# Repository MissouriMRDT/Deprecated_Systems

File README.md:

<<<<<<< HEAD
# Deprecated-Systems
 Deprecated sub-system repositories that have no present day equivalent

How to add repos to this: 

1) Make branch on here for the repo you're about to copy in
2) Clone this repo onto your pc
3) Make sure that you've merged all branches on the deprecated repo into master, this process only preserves its master
4) in gitshell inside of the Deprecated-Systems folder:

git checkout [name of branch you're going to copy the repo into]

git remote add x [url of deprecated repo]

git fetch x

git merge x/master --allow-unrelated-histories

git remote rm x

5) delete old branch

=======
Battery-Management-System
=========================

Battery Management System with integrated CC and CV charge control and passive cell balancing.
>>>>>>> x/master

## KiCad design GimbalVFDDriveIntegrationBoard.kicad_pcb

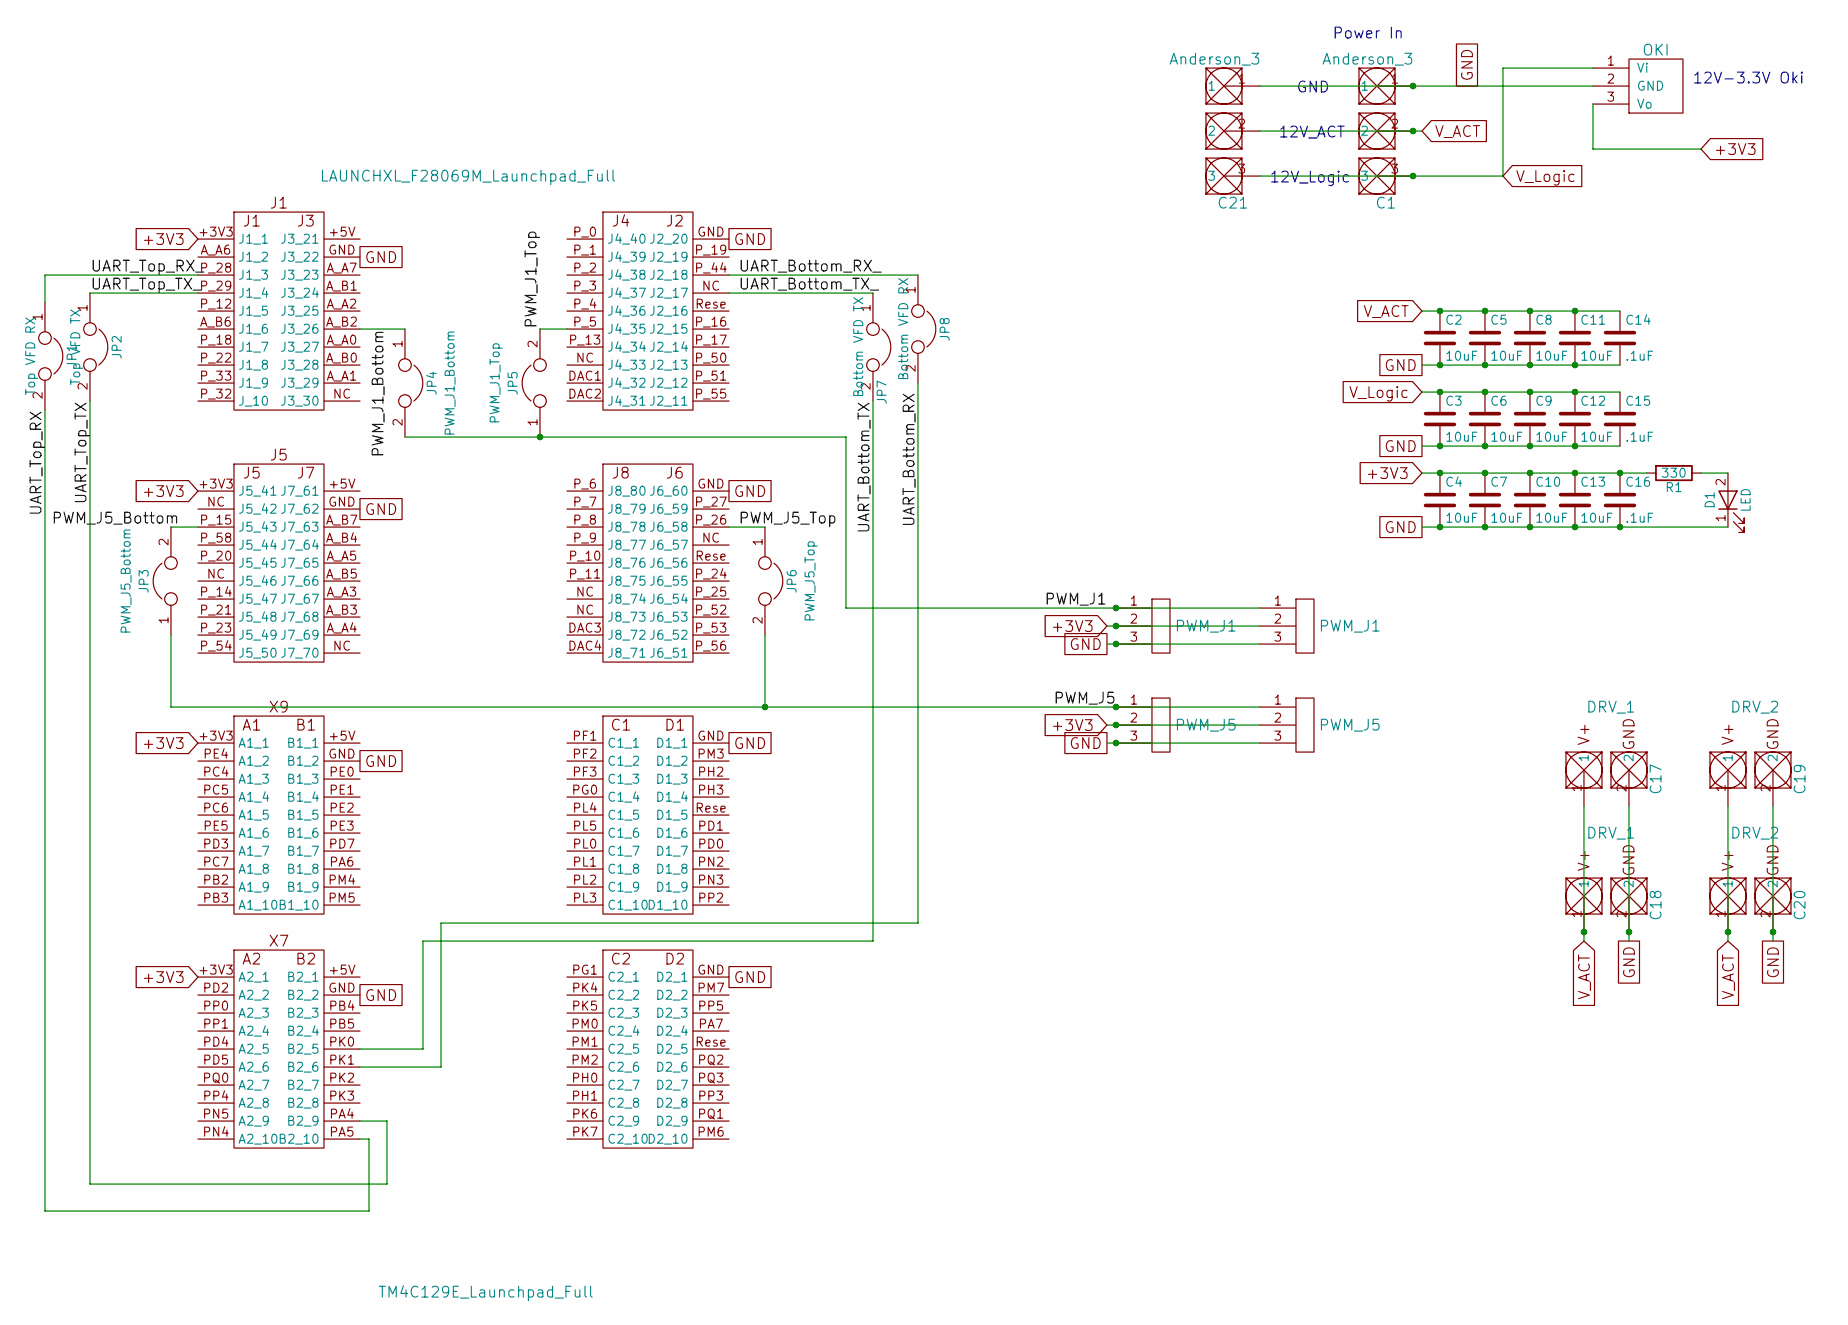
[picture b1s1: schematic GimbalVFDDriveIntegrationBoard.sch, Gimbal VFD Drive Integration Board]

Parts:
C1, C21: Anderson_3; Anderson_3_Horisontal_Side_by_Side
C2, C3, C4, C5, C6, C7, C8, C9, C10, C11, C12, C13: 10uF; C_0603_HandSoldering
C14, C15, C16: .1uF; C_0603_HandSoldering
C17, C18: DRV_1; Anderson_2_Horisontal_Side_by_Side
C19, C20: DRV_2; Anderson_2_Horisontal_Side_by_Side
D1: LED; LED_1206_HandSoldering
JP1: Top VFD RX; Pin_Header_Straight_1x02_Pitch1.27mm
JP2: Top VFD TX; Pin_Header_Straight_1x02_Pitch1.27mm
JP3: PWM_J5_Bottom; Pin_Header_Straight_1x02_Pitch1.27mm
JP4: PWM_J1_Bottom; Pin_Header_Straight_1x02_Pitch1.27mm
JP5: PWM_J1_Top; Pin_Header_Straight_1x02_Pitch1.27mm
JP6: PWM_J5_Top; Pin_Header_Straight_1x02_Pitch1.27mm
JP7: Bottom VFD TX; Pin_Header_Straight_1x02_Pitch1.27mm
JP8: Bottom VFD RX; Pin_Header_Straight_1x02_Pitch1.27mm
R1: 330; R_0603_HandSoldering
U1: LAUNCHXL_F28069M_Launchpad_Full; LAUNCHXL_F28069M_Launchpad_FULL_Booster_SMD
U2: TM4C129E_Launchpad_Full; TM4C129E_Launchpad_FULL_Booster_Bottom_SMD
U3, U5: PWM_J1; MOLEX_SL_3_Horizontal
U4, U6: PWM_J5; MOLEX_SL_3_Horizontal
U7: OKI; OKI_Horisontal

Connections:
+3V3: C4.1, C7.1, C10.1, C13.1, C16.1, R1.2, U1.+3V3 (J1_1), U2.+3V3 (A1_1), U3.2, U4.2, U5.2, U6.2, U7.3 (Vo)
/PWM_J1: JP4.2, JP5.1, U3.1, U5.1
/PWM_J1_Bottom: JP4.1, U1.A_B2 (J3_26)
/PWM_J1_Top: JP5.2, U1.P_5 (J4_35)
/PWM_J5: JP3.1, JP6.2, U4.1, U6.1
/PWM_J5_Bottom: JP3.2, U1.P_15 (J5_43)
/PWM_J5_Top: JP6.1, U1.P_26 (J6_58)
/UART_Bottom_RX: JP8.2, U2.PK1 (B2_6)
/UART_Bottom_RX_: JP8.1, U1.P_44 (J2_18)
/UART_Bottom_TX: JP7.2, U2.PK0 (B2_5)
/UART_Top_RX: JP1.2, U2.PA5 (B2_10)
/UART_Top_RX_: JP1.1, U1.P_28 (J1_3)
/UART_Top_TX: JP2.2, U2.PA4 (B2_9)
/UART_Top_TX_: JP2.1, U1.P_29 (J1_4)
GND: C1.1, C2.2, C3.2, C4.2, C5.2, C6.2, C7.2, C8.2, C9.2, C10.2, C11.2, C12.2, C13.2, C14.2, C15.2, C16.2, C17.2, C18.2, C19.2, C20.2, C21.1, D1.1 (K), U1.GND (J2_20), U2.GND (B1_2), U3.3, U4.3, U5.3, U6.3, U7.2 (GND)
unnamed: D1.2 (A), R1.1
unnamed: JP7.1, U1.NC (J2_17)
V_ACT: C1.2, C2.1, C5.1, C8.1, C11.1, C14.1, C17.1, C18.1, C19.1, C20.1, C21.2
V_Logic: C1.3, C3.1, C6.1, C9.1, C12.1, C15.1, C21.3, U7.1 (Vi)

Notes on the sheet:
Power In
12V_ACT
12V_Logic
GND
12V-3.3V Oki

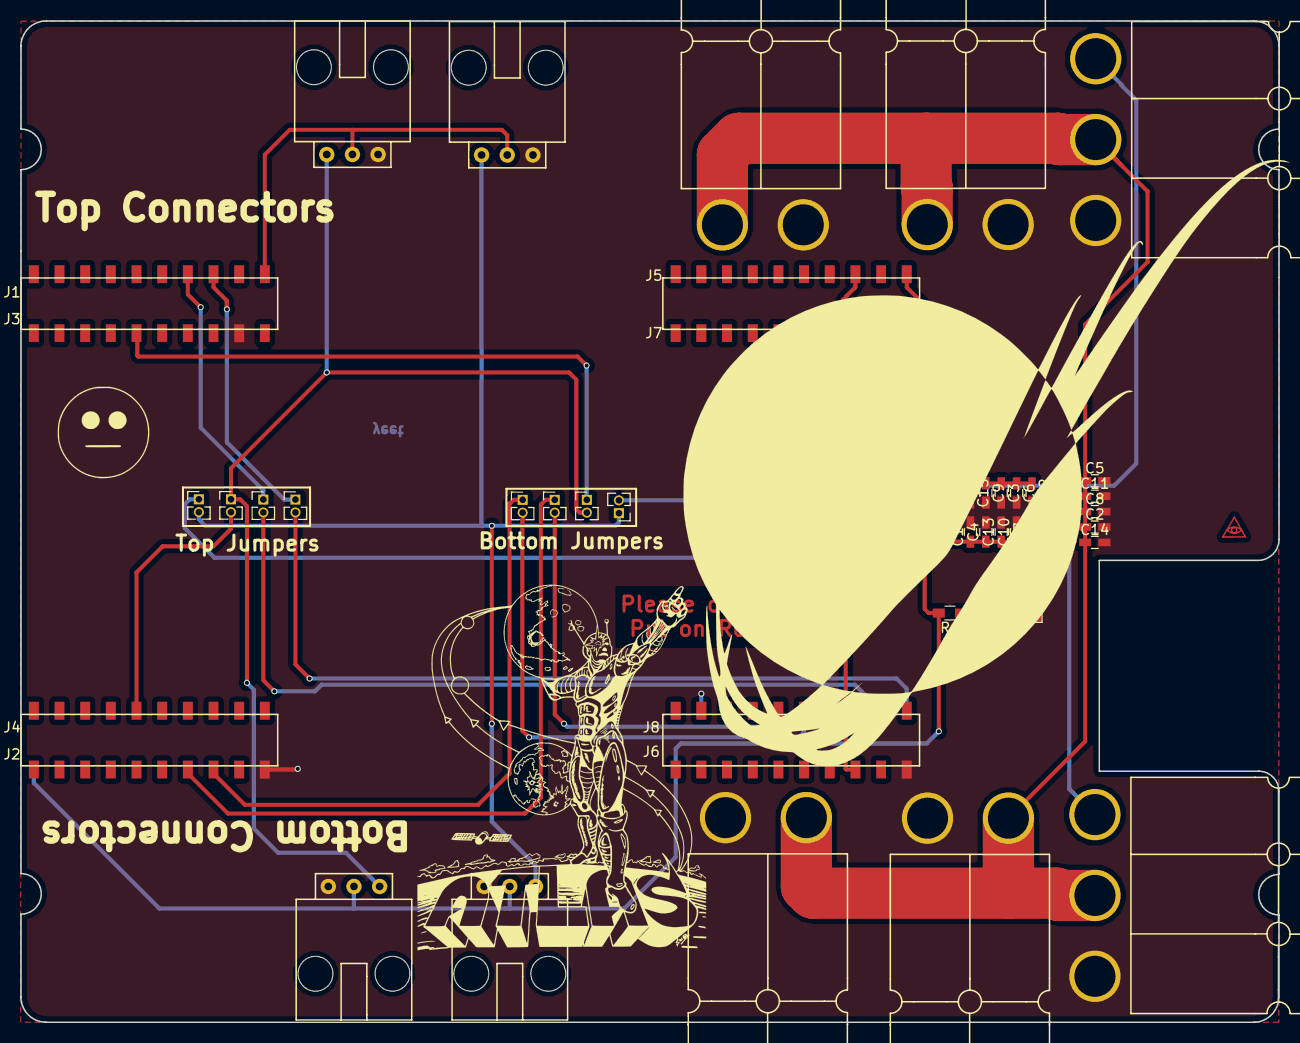
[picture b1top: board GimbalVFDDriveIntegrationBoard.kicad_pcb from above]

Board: 2 copper layers, 124.5 x 99.1 mm, 38 parts (0 on the bottom side), 19 nets.

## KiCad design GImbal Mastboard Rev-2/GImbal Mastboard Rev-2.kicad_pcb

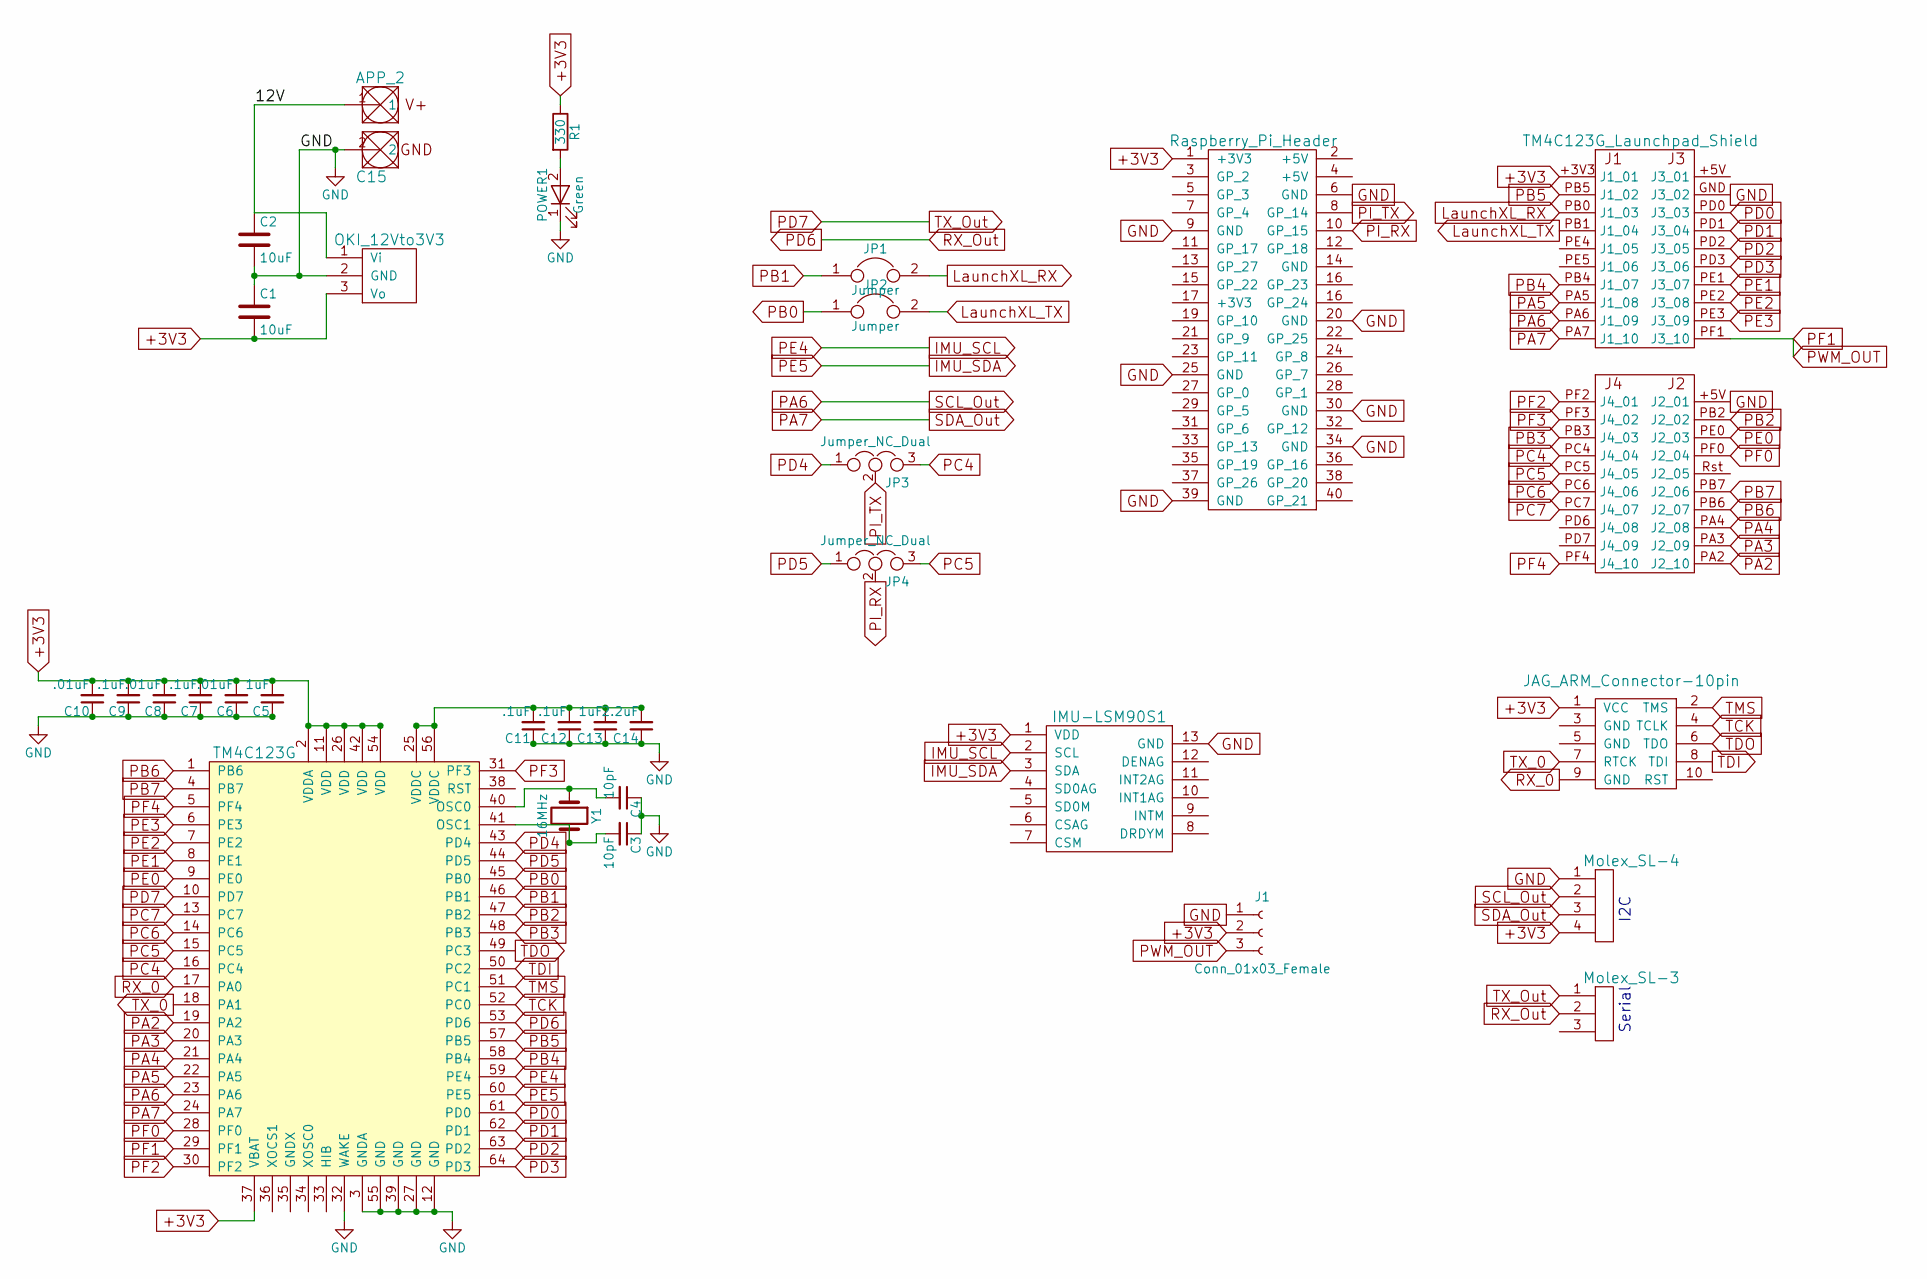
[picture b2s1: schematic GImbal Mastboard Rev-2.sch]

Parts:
C1, C2: 10uF; C_0603_HandSoldering
C3, C4: 10pF; C_0603_HandSoldering
C5, C13: 1uF; C_0603_HandSoldering
C6, C8, C10: .01uF; C_0603_HandSoldering
C7, C9, C11, C12: .1uF; C_0603_HandSoldering
C14: 2.2uF; C_0603_HandSoldering
C15: APP_2; Anderson_2_Horisontal_Side_by_Side
J1: Conn_01x03_Female; Socket_Strip_Straight_1x03_Pitch2.54mm
JP1, JP2: Jumper; Pin_Header_Straight_1x02_Pitch2.54mm
JP3, JP4: Jumper_NC_Dual; Pin_Header_Straight_1x03_Pitch2.54mm
POWER1: Green; LED_1206_HandSoldering
R1: 330; R_0603_HandSoldering
U1: TM4C123G; TQFP-64_10x10mm_Pitch0.5mm
U2: OKI_12Vto3V3; OKI_Horisontal
U3: IMU-LSM90S1; IMU_LSM90S1
U4: Raspberry_Pi_Header; RASPBERRY_PI_HEADERS
U5: TM4C123G_Launchpad_Shield; TM4C123G_Booster
U6: JAG_ARM_Connector-10pin; JTAG_ARM_Connector_10_Pin
U7: Molex_SL-4; MOLEX_SL_4
U8: Molex_SL-3; MOLEX_SL_3
Y1: 16MHz; CRYSTAL_SMT

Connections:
+3V3: C1.2, C5.2, C6.2, C7.2, C8.2, C9.2, C10.2, J1.2, R1.1, U1.2 (VDDA), U1.11 (VDD), U1.26 (VDD), U1.37 (VBAT), U1.42 (VDD), U1.54 (VDD), U2.3 (Vo), U3.1 (VDD), U4.1 (+3V3), U5.+3V3 (J1_01), U6.1 (VCC), U7.4
/12V: C2.1, C15.1, U2.1 (Vi)
GND: C1.1, C2.2, C3.1, C4.1, C5.1, C6.1, C7.1, C8.1, C9.1, C10.1, C11.1, C12.1, C13.1, C14.1, C15.2, J1.1, POWER1.1 (K), U1.3 (GNDA), U1.12 (GND), U1.27 (GND), U1.32 (WAKE), U1.39 (GND), U1.55 (GND), U2.2 (GND), U3.13 (GND), U4.6 (GND), U4.9 (GND), U4.20 (GND), U4.25 (GND), U4.30 (GND), U4.34 (GND), U4.39 (GND), U5.+5V (J2_01), U5.GND (J3_02), U7.1
IMU_SCL: U1.59 (PE4), U3.2 (SCL)
IMU_SDA: U1.60 (PE5), U3.3 (SDA)
LaunchXL_RX: JP1.2, U5.PB0 (J1_03)
LaunchXL_TX: JP2.2, U5.PB1 (J1_04)
unnamed: C3.2, U1.41 (OSC1), Y1.2
unnamed: C4.2, U1.40 (OSC0), Y1.1
unnamed: C11.2, C12.2, C13.2, C14.2, U1.25 (VDDC), U1.56 (VDDC)
unnamed: POWER1.2 (A), R1.2
PA2: U1.19 (PA2), U5.PA2 (J2_10)
PA3: U1.20 (PA3), U5.PA3 (J2_09)
PA4: U1.21 (PA4), U5.PA4 (J2_08)
PA5: U1.22 (PA5), U5.PA5 (J1_08)
PA6: U1.23 (PA6), U5.PA6 (J1_09), U7.2
PA7: U1.24 (PA7), U5.PA7 (J1_10), U7.3
PB0: JP2.1, U1.45 (PB0)
PB1: JP1.1, U1.46 (PB1)
PB2: U1.47 (PB2), U5.PB2 (J2_02)
PB3: U1.48 (PB3), U5.PB3 (J4_03)
PB4: U1.58 (PB4), U5.PB4 (J1_07)
PB5: U1.57 (PB5), U5.PB5 (J1_02)
PB6: U1.1 (PB6), U5.PB6 (J2_07)
PB7: U1.4 (PB7), U5.PB7 (J2_06)
PC4: JP3.3, U1.16 (PC4), U5.PC4 (J4_04)
PC5: JP4.3, U1.15 (PC5), U5.PC5 (J4_05)
PC6: U1.14 (PC6), U5.PC6 (J4_06)
PC7: U1.13 (PC7), U5.PC7 (J4_07)
PD0: U1.61 (PD0), U5.PD0 (J3_03)
PD1: U1.62 (PD1), U5.PD1 (J3_04)
PD2: U1.63 (PD2), U5.PD2 (J3_05)
PD3: U1.64 (PD3), U5.PD3 (J3_06)
PD4: JP3.1, U1.43 (PD4)
PD5: JP4.1, U1.44 (PD5)
PD6: U1.53 (PD6), U8.2
PD7: U1.10 (PD7), U8.1
PE0: U1.9 (PE0), U5.PE0 (J2_03)
PE1: U1.8 (PE1), U5.PE1 (J3_07)
PE2: U1.7 (PE2), U5.PE2 (J3_08)
PE3: U1.6 (PE3), U5.PE3 (J3_09)
PF0: U1.28 (PF0), U5.PF0 (J2_04)
PF1: J1.3, U1.29 (PF1), U5.PF1 (J3_10)
PF2: U1.30 (PF2), U5.PF2 (J4_01)
PF3: U1.31 (PF3), U5.PF3 (J4_02)
PF4: U1.5 (PF4), U5.PF4 (J4_10)
PI_RX: JP4.2, U4.10 (GP_15)
PI_TX: JP3.2, U4.8 (GP_14)
RX_0: U1.17 (PA0), U6.9 (GND)
TCK: U1.52 (PC0), U6.4 (TCLK)
TDI: U1.50 (PC2), U6.8 (TDI)
TDO: U1.49 (PC3), U6.6 (TDO)
TMS: U1.51 (PC1), U6.2 (TMS)
TX_0: U1.18 (PA1), U6.7 (RTCK)

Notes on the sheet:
I2C
Serial

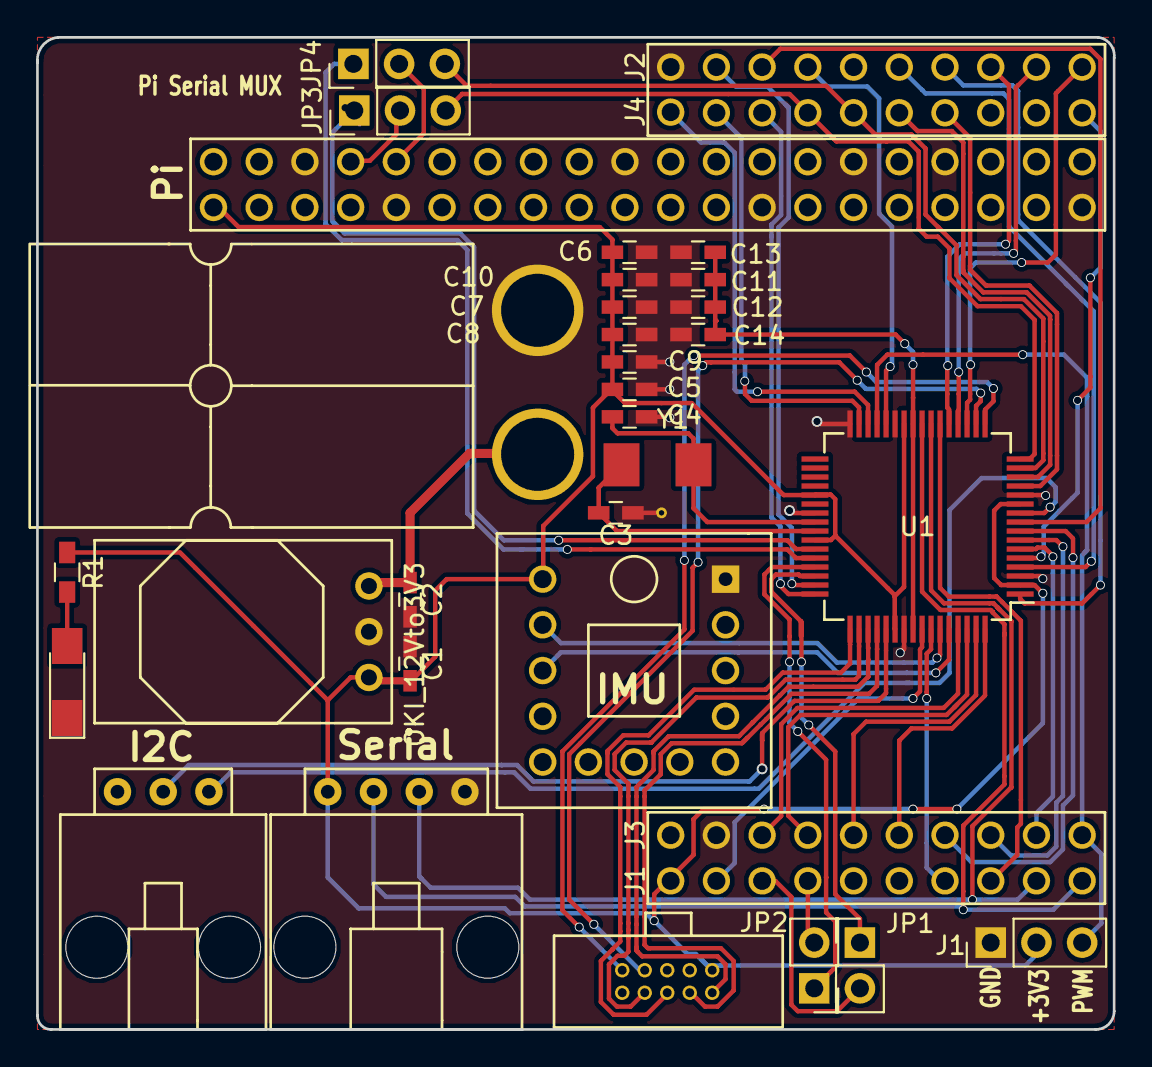
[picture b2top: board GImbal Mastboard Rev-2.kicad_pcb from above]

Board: 2 copper layers, 59.8 x 55.1 mm, 31 parts (0 on the bottom side), 54 nets.

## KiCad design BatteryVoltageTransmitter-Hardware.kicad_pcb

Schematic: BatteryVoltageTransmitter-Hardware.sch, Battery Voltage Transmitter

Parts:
D1: LED; LED_0603_HandSoldering
R1: 100; R_0805_HandSoldering
S1: MRDT_Logo; MRDT_Logo_7.5mm
U1: MSP_EXP432P401R_Launchpad_Shield; MSP_EXP432P401R_Launchpad_FULL_Booster
U2: Raspberry_Pi; RASPBERRY_PI_HEADERS

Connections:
+5V: R1.2, U1.21 (5V), U2.2 (+5V), U2.4 (+5V)
GND: D1.1 (K), U1.20 (GND), U1.22 (GND), U2.6 (GND), U2.9 (GND), U2.14 (GND), U2.20 (GND), U2.25 (GND), U2.30 (GND), U2.34 (GND), U2.39 (GND)
MSP432_TX_to_PI_RX: U1.34 (P2.3), U2.10 (GP_15)
unnamed: D1.2 (A), R1.1

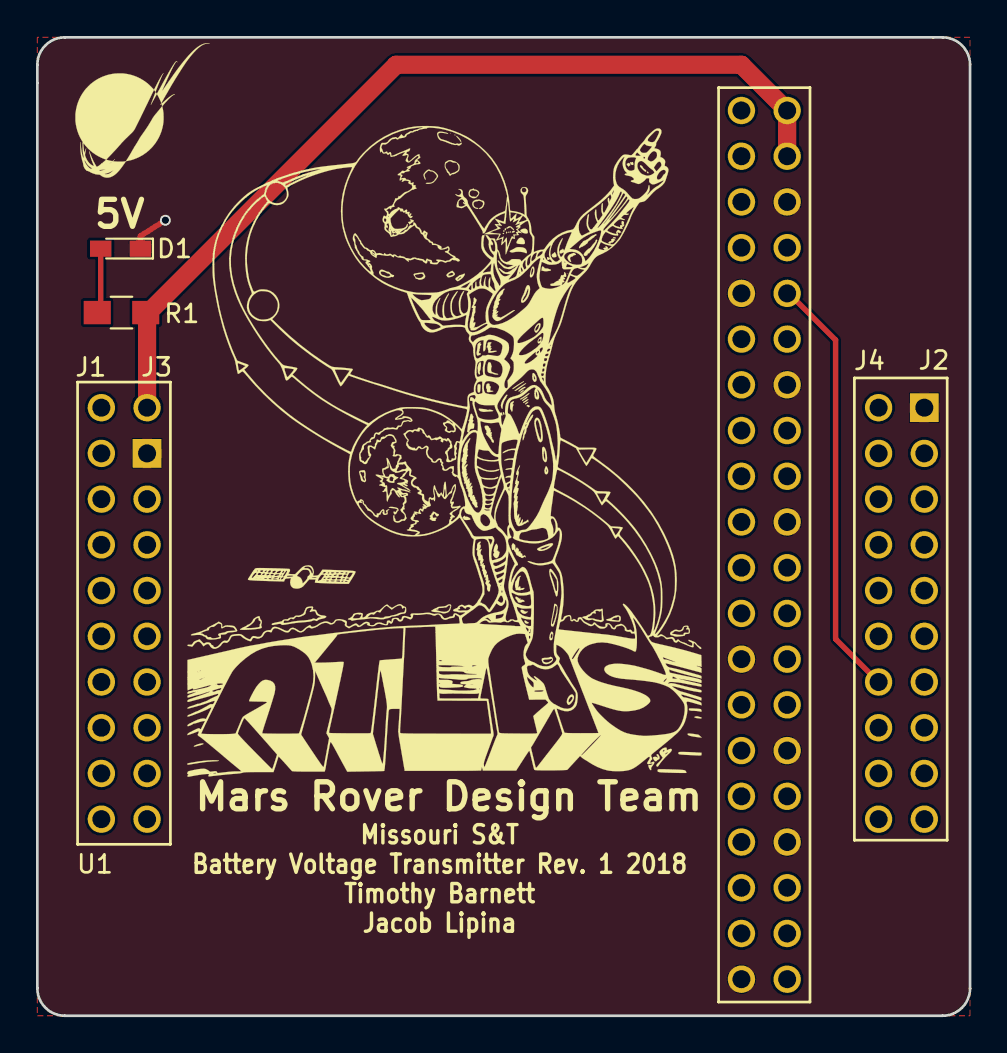
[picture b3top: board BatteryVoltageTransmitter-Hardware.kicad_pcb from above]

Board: 2 copper layers, 51.8 x 54.4 mm, 6 parts (0 on the bottom side), 4 nets.

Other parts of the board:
S2: Logo_or_Signature; Atlas_Logo_28.6mmX37.3mm

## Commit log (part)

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2016-10-25 Updated Gitignore and removed stray file
2016-10-25 Finished routing Dropbay Connectors
2016-10-27 Code standard changes, more comments.
2016-10-28 Implemented read and graph of spectrometer data.
2016-11-03 Updated template area to latest template
2016-11-04 Added 12V Actuation to run servos
2016-11-04 Updated Donation Address
2016-11-05 Added LSM9DS1 IMU to MRDT-Sensors
2016-11-06 Completed Rev 1 of Science Board
    Added second sensor board and completed board design.
2016-11-06 Rounded corners of board
2016-11-06 Edits after review
    Complete rearrangement of board to put circuitry under Tiva, with
    horizontal connectors. Changed layout of photodiode amplifier circuit to
    reduce noise. Added mounting holes and rounded corners. Replaced I2C
    level shifter IC. tided up traces and component names.
2016-11-07 Stitched GNDs better
2016-11-07 Added SL02-Horiz
2016-11-08 Changed drill size for Vias to 12mil
2016-11-08 Add SL5 connectors for motors, passthrough serial data
    Motors get independent control in normal mode, tank steer (left together, right together) in failover mode
2016-12-03 Converted DropBay control to use an array of Servos
2016-12-16 update gitignore
2016-12-16 Weather and Soil Sensor boards
2017-01-05 Add tab to display pictures
2017-01-07 Added name to test point package
2017-01-08 Finished routing and labeled board
2017-01-10 Updated LXDC2HN
2017-01-12 Completed board review #1 revisions
2017-01-12 Board Review revisions completed
2017-01-21 Add images to directory and add functionality to import png images
2017-01-27 Test app functionality for science board
    Test app to control flap, laser, carousel, other functions. in
    development
2017-02-02 Create show picture funciton
2017-02-03 Updated to match ordered Ext Controls board
    Made Vias Smaller
    Moved Ethernet Circuitry lower
    Added Actuation Bus
    Updated Libraries
    Rounded Board Corners
2017-02-03 Added Max4312 chip to schematic
2017-02-03 Added Molex BNC
2017-02-04 added opamp
2017-02-04 Testing science board things
    minor changes
2017-02-10 Remove arm.h, update science board code
2017-02-15 Added dynamixel connector and serial line
2017-02-25 Orgainize Test Sketches into one folder
2017-03-01 Tested and fixed these sketches.
    I have seen these work!
2017-03-02 added arm board V2's 3.3V lin reg
2017-03-04 Added more comments to improve readability
    Added comments for functions, control blocks, and the mail execution
    loop, Added TODO: coments
2017-03-09 Traces for Dynamixels and extra PWMs
2017-03-14 added arm board inductor
2017-03-15 Make Cmd ID enum, added millis sensor delay
    Enumerated command Data for science commands, added delay between sensor
    reads, initialized all sensors to off
2017-03-18 Switch main motor driver, fixed issues with 3V3
2017-03-20 Integrated weather sensor board, started soil sensor integration, changed spectrometer motor driver
2017-03-21 Quick + basic RPi hat
2017-03-22 some changes from board review
    > remove diodes for LEDs
    > space out FETs
    > separate grounds for FETs
    > Move vias out from under FETs
2017-03-22 Removed unnecessary 3v3 net and swapped header with eagle standard part
2017-03-23 made changes related to board review
2017-03-23 Widened board and spaced out connectors
2017-03-23 Changes to Arm board
    Fixed text, added divider resistors to sensors, added power LED, rearranged schematic slightly
2017-03-23 Added the actual program file for arm
    Added the actual science arm main program
2017-03-23 adjustable regulator for laser
    BA00DD0WHFP-TR
2017-03-23 changed tiva pins for soil sensors
2017-03-23 Rerouted 12V_ACT for better planes
2017-03-23 ONE MORE I SWEAR
    fixed airwire.
2017-03-23 Updated Revision text
2017-03-23 finished gimbal breakout
    added mounting holes
    labeled board
    fixed traces
2017-04-02 Debug Work - flap and serial comm
    switched flap open and close angles
    tweaked flap open and close angles
    commented out annoying print messages
2017-04-03 Basic functionality for soil temperature and humidity readings as well as spectrometer are implemented and elementary test confirmed.
2017-04-04 Four pictures input as a 2x2 grid on the picture tab.
2017-04-05 Small changes
2017-04-05 Dynamixel LED blinking for debugging (untested)
2017-04-06 Modify to account for Gryphon graphs (Gryphs? Graphon?). Untested with real data. Add QOL picture features (fullscreen, browsed file input)
2017-04-06 Both gimbals fully functional
2017-04-09 changes due to new science board
    testing for carousel, new pins
2017-04-13 add this file
    add this file
2017-04-22 fixed main gimabal serial, and added untested menu functionality
2017-04-22 Code Review 2, Updated TODOs
    Second Code Review, 4/22/17, Updated TODOs in arm board and science
    board
2017-04-23 adding sensor code to science and sci-arm
    copied code from sensor test sketches into science.ino and arm.ino/arm.h
    init all sensor pins for input
    set sensor pins in header file
2017-04-28 added sensor functions to arm board and clean up science.ino
    add ability for continuous data to science arm board, clean up
    code/better organize it ☺
2017-04-29 added AZ1117EH-5.0
2017-05-09 Defined Pins, Added Config, Matched CommandIDs
    Defined Pins in header files, Added Configuration File for Future Sensor
    Calibration, Matched Command IDs to the current RED version
2017-05-15 TCP for phot data and data ids for arm
    :+1:
2017-05-23 updated parameters and tested sample data
2017-05-23 Added Drop Bay close capability
2017-05-24 Added end of year stuff and fixed change to sensor names
2017-05-25 updated carabiner code
2017-05-26 Started implementing new data processing method
2017-05-26 plotted spectrometer data
2017-05-26 Corrected diode switch
2017-05-27 Fixed carabiner value check
2017-09-12 Pre-repo progress commit
2017-09-14 Spectra should be working properly.
2017-09-15 Requests for weather, soil, spectrometer, all working.
2017-09-23 Add functionality to insert raw spectra
2017-09-23 Subscribe to all IP addresses from our configuration file
2017-09-24 Finished adding comps and changing labels
    All components that will be on gimbal pwer board have been added and wires have been renamed to match gimbal design. Last schematic change to make is label header pins.
2017-09-28 Upgrade from PyQt4 to PyQt5.
2017-09-29 Added the 74LVC 2-1 Demux
    Added 2-1 demux and fixed some of the packages added in previous commit
    (added pin 1 markers).
2017-10-01 Added grounds for the acs781
2017-10-01 specroprocessing
2017-10-01 Header pins to control card named
    All traces that will go to control card have been named on a header pin and can be rearanged for more convienent layout. Power indication simplified.
2017-10-01 C2000 Launchpad Schematic and Board
    C2000 CAD files
2017-10-08 Deleted accidental Eagle files
2017-10-13 The motor controller driver for powerboard is ready for rev 1
    This is the complete powerboard design based off of what was decided at the Gimbal meetings. The actual schematic for the board is simply 1A.sch and the board design is 1A.brd I did change some pin a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
2017-10-15 Capacitor fixed
    Hole outline was on the wrong layer
2017-10-16 Started deleting unnecessary hardware on F28069M
    Matched pinout from 28027F with pins on 28069M and deleted all remeaining unnecessary pins. Deleted the debugging and flashing hardware. Decided to delete all muxes and logic gates because we believe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
2017-10-19 Added F28069M Microcontroller
    Took Ti's schematic and board and deleted unecessary functionality. We are using what remains as an integrated version of the F28069M.
2017-10-19 Deleted lock
    My eagle keeps adding locks to my files, which may prevent other people from opening the files, I'm not really sure.
2017-10-20 Named GPIO and ADC pins on F28069M
    Still need to sort out errors identified by ERC.
2017-10-21 Removed Temp Files
2017-10-21 Rearanged Board and rounded edges
    Put Anderson Connectors in correct places as well as rewired the whole board. I then rounded the corners of the board and put wholes in the board so we could properly mount it. Eagle would not allow 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
2017-10-28 Initialize subscriber array with null ip addresses / data id's
2017-10-29 Got width standardized
    Every wire and polygon now has a width of 16 mil
2017-10-29 Fets are now foldable
    Had to move caps around to get fets ample space to be able to be folded down under the board. Approximately 20mm of space. Will still need changes as top chip is finished. Power now has to round seve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
2017-10-30 layout for control card created
    Placed large components, now placing placing passive components individually and routing
2017-11-02 Quick Routing and Labeling Fix
    Straigtenned header names and made sure polygons stretched to same length on board.
2017-11-04 Added Silkscreen and Bill of Materials
    Bill of materials is now added and can be changed as time goes on. All objects on board have been smashed and names are fairly visible. Some areas around phase C are hard to read due to spacing. Silk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
2017-11-04 Fixed some spacing issues
    Moved a wire and straigtenned some polygons for a tighter board.
2017-11-04 more finishing touches.
2017-11-06 Deleted brd and edited schematic
2017-11-07 finsihed simple connections. All devices are on board. Still a lot of pins on header that need to be connected to microprocessor. A lot of them cross. Not sure if possible without vias.
2017-11-08 All the routing is finished. It needs some serious cleaning up and there are most likely mistakes.
2017-11-14 Added BOM and order sheet, modified Board Layout
2017-11-14 Updated Gerber Files; Final changes to board design
2017-11-16 Drill Board: Starting from a clean slate (power and filtering only)
2017-12-02 Fixed formatting for google doc initial push.
2017-12-02 Made data, data_byte_count, and data_id zero in Rovecomm_recieve. UNTESTED
2017-12-09 Fixed some naming errors and moved all funcions out of _init_
2017-12-09 Make Readme formatting nicer
2017-12-30 Added SL connectors & MAX232, added Andrew's JTAG connector
    Added SL connectors from gimbal power board and added connections to BOOSTXL header / MAX232. Same implementation as gimbal power board.
2018-01-01 Improved Interface Documentation
2018-01-04 Finished Routing Board
    Board is finished with routing, however it needs silkscreen to be done. Silk screen will be completed at a later date. There is one unbroken ground plain. Top plain is fairly broken as a ground plane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
2018-01-14 Remved unnecesary files
    BOM and connection information moved to Google Drive under 2018-->Rovecore Electrical-->Programmer Board
2018-01-15 Updated silkscreen and moved reset switch
    The board was shrunken for better fitting with boards that this card will be compatible with. Reset switch was moved to accomodate this. The Jtag connector routing was fixed due to a placement error.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
2018-01-20 Did a little comment reformatting
2018-01-20 first training
2018-01-23 Routing and Silkscreen Update
    New routes were made and Silkscreen changes were made. SL connectors are now labelled and arrows indicate direction of headers.
2018-01-24 Updated schematic and board for final board review
    Changed oscilator for ATMEGA
    changed power to ATMEGA to 3.3V
    Cleaned up position and traces
    Added mounting holes
    Added signature and board data
2018-01-24 Removed redundant SL connector, restructured right side of board and reduced board size
2018-01-25 Rev 3 Gerbs created
2018-01-25 Control Card Routing Update
    Connected VCC to all necessary parts.
2018-01-27 Routing Update
    Board's routing was completely redone and is much more efficient with plenty of vias connecting the ground planes.
2018-01-28 Small Via changes
2018-01-31 Created Gerbs
2018-02-04 Updated read me
2018-02-04 readme
2018-02-04 Master read me
2018-02-04 Revert "Added JLCPCB CAM files"
    This reverts commit 26ec2af4e529b2b3f0f422ca2c6a6f543a598df3.
2018-02-10 Fixed spelling of receiveFrom()
2018-02-11 recv_header=True for rove db on recvFrom
2018-02-18 Finished Board Wiring
2018-02-24 Modified board
2018-03-11 Added Schematic and Layout
2018-03-12 Added PWM Output on Headers as backup if serial does not work.
2018-03-17 Made naming changes that may mess things up...
    renamed all components with dashes to us underscores
2018-03-19 Removed Report
2018-04-01 sorting for archiving
2018-04-02 restructuring for archiving
2018-04-21 began to match this year's pins
